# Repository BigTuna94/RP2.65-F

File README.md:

# RP2.65-F
An 65% Ortholinear Keyboard based on the Rasperry Pi RP2040 with faders.

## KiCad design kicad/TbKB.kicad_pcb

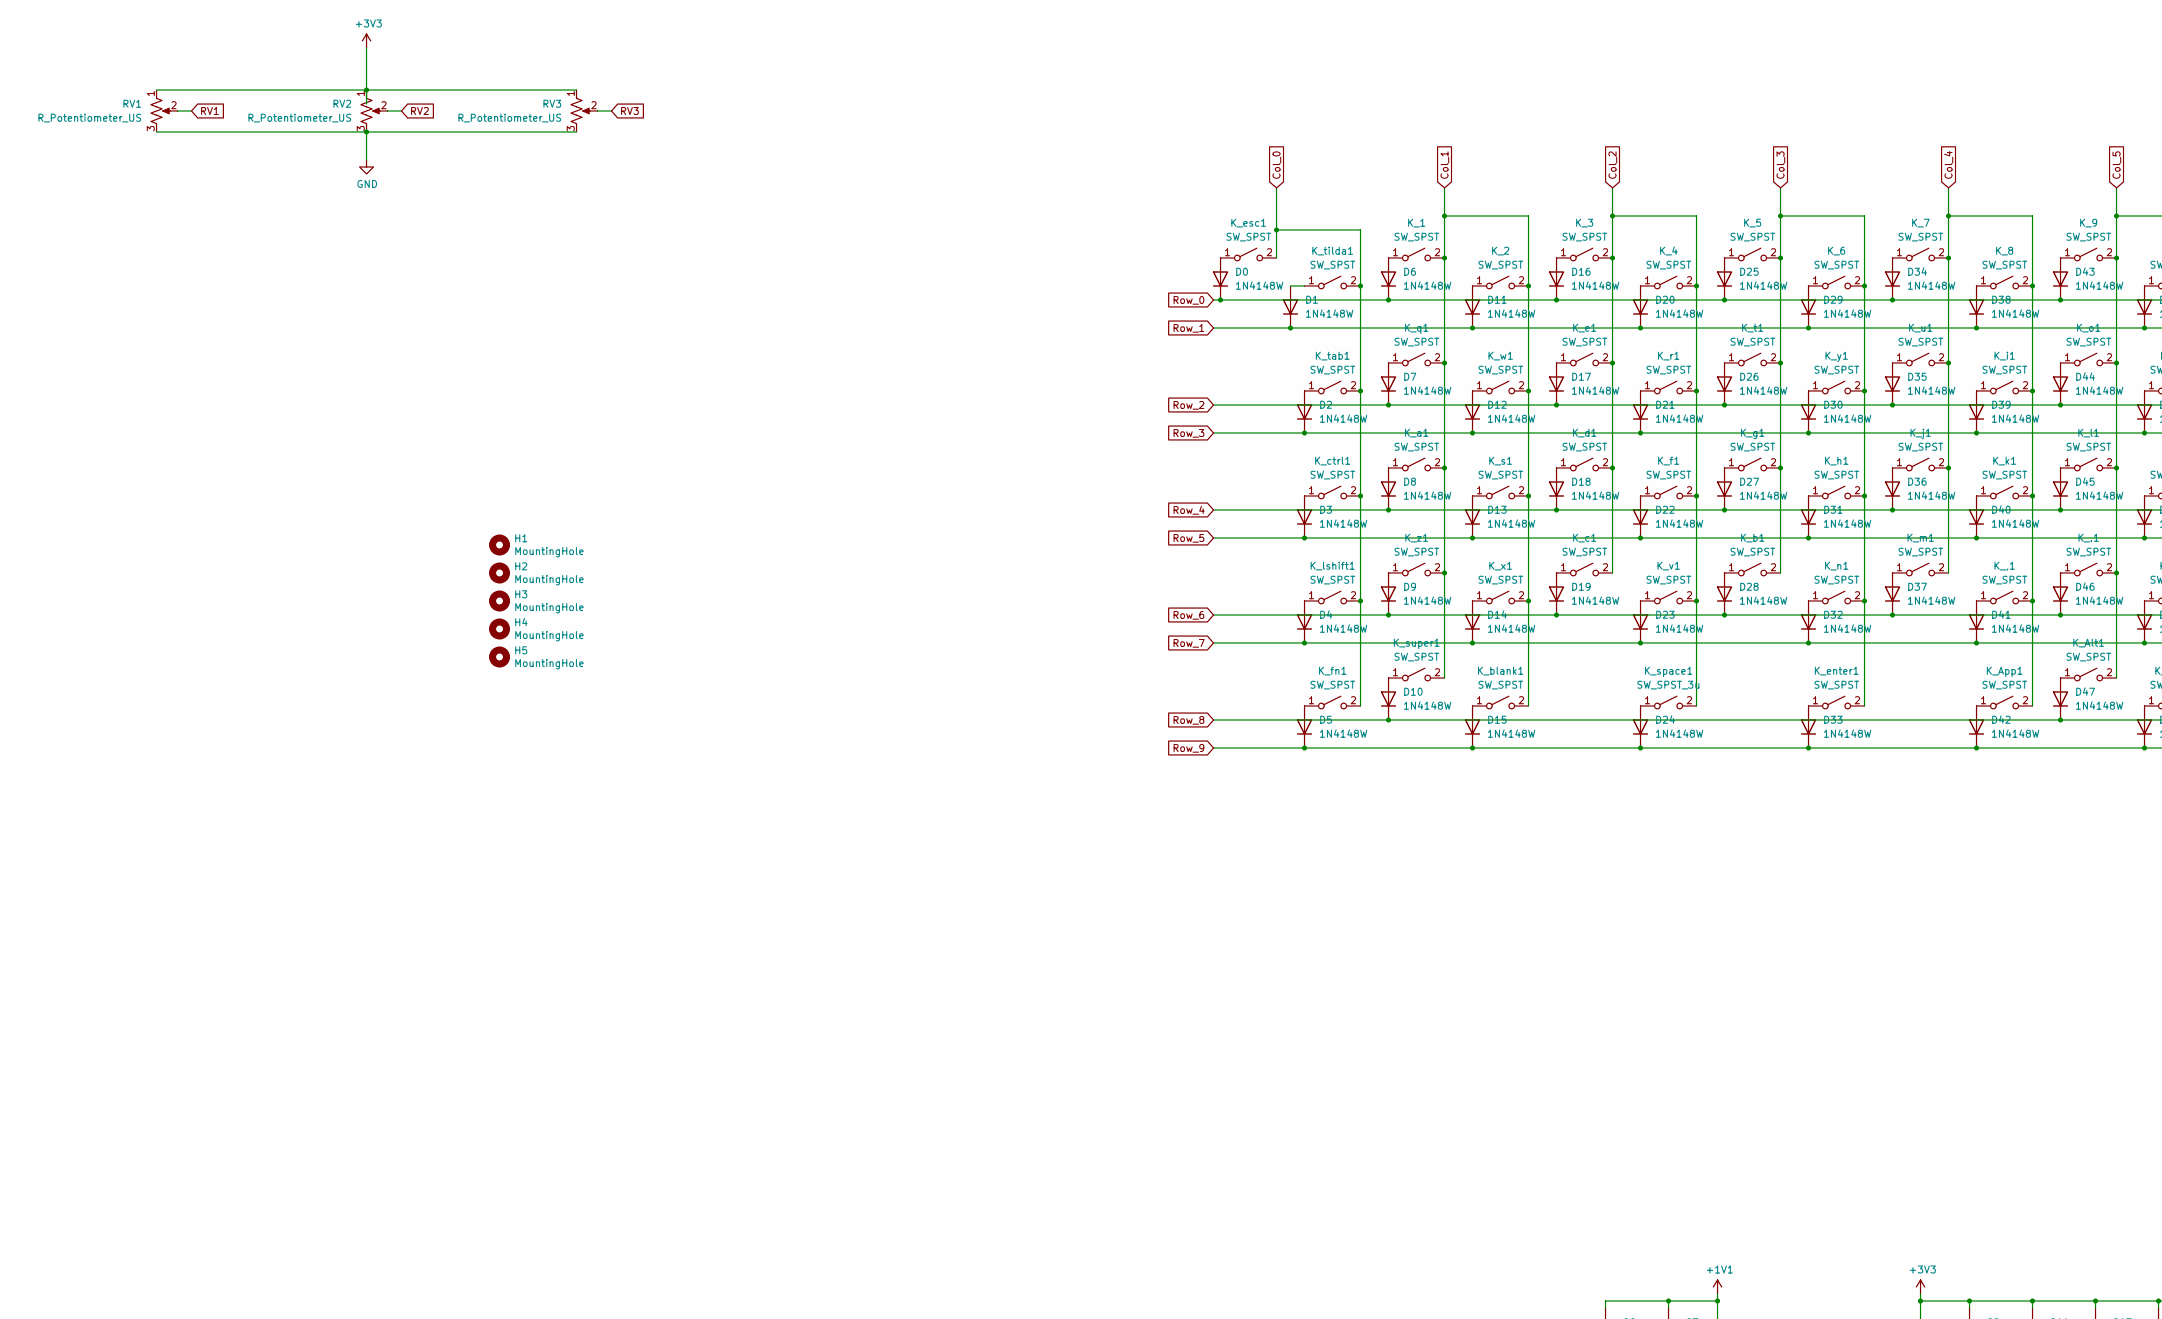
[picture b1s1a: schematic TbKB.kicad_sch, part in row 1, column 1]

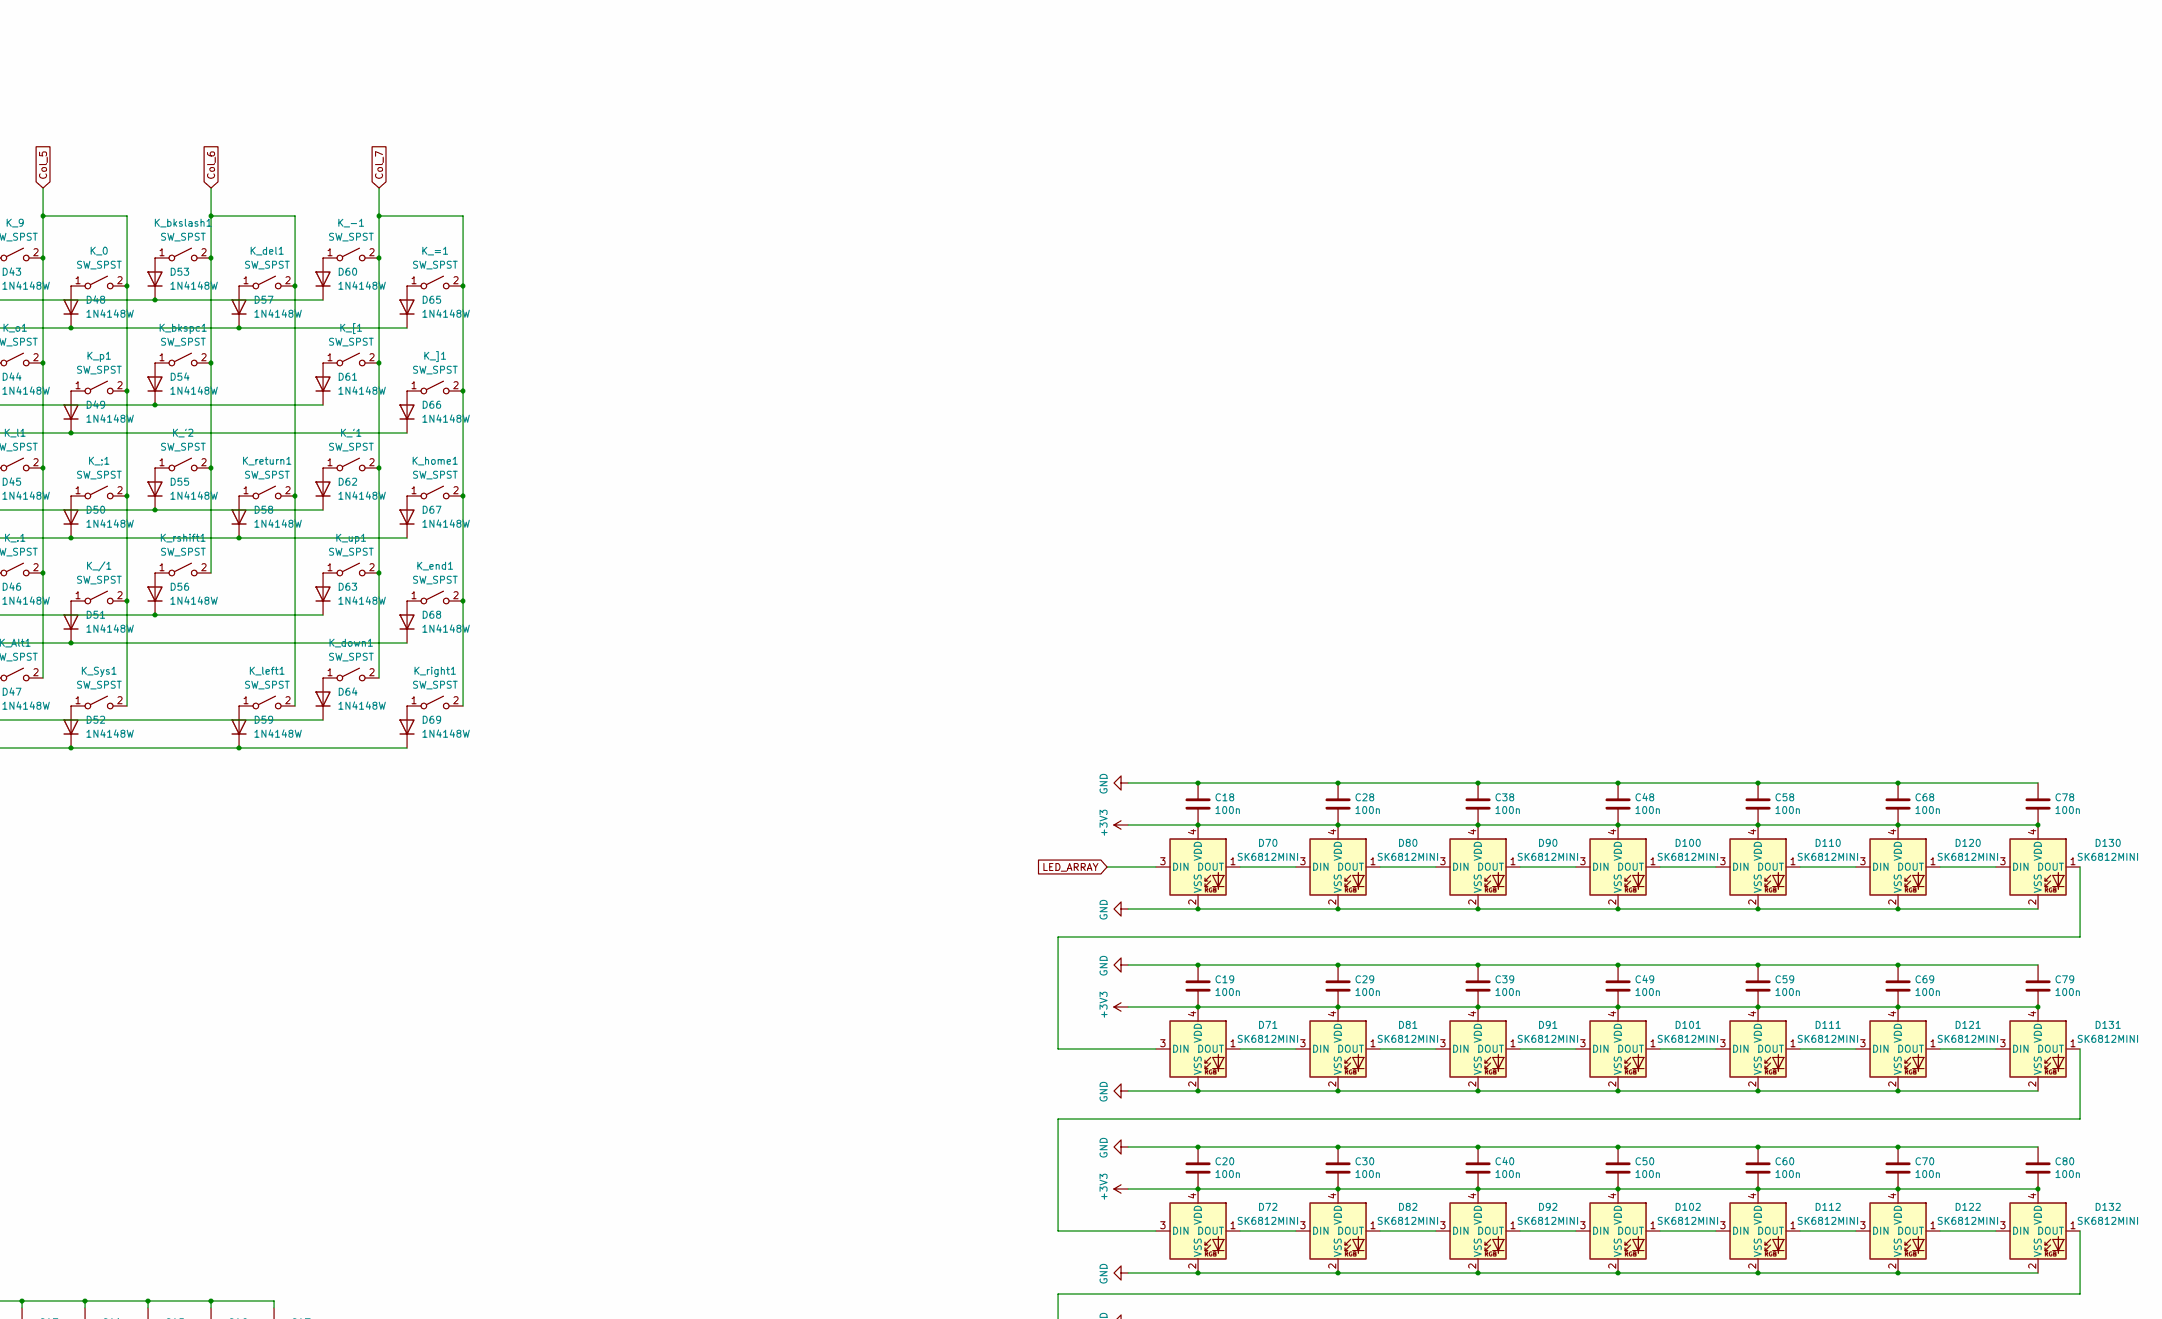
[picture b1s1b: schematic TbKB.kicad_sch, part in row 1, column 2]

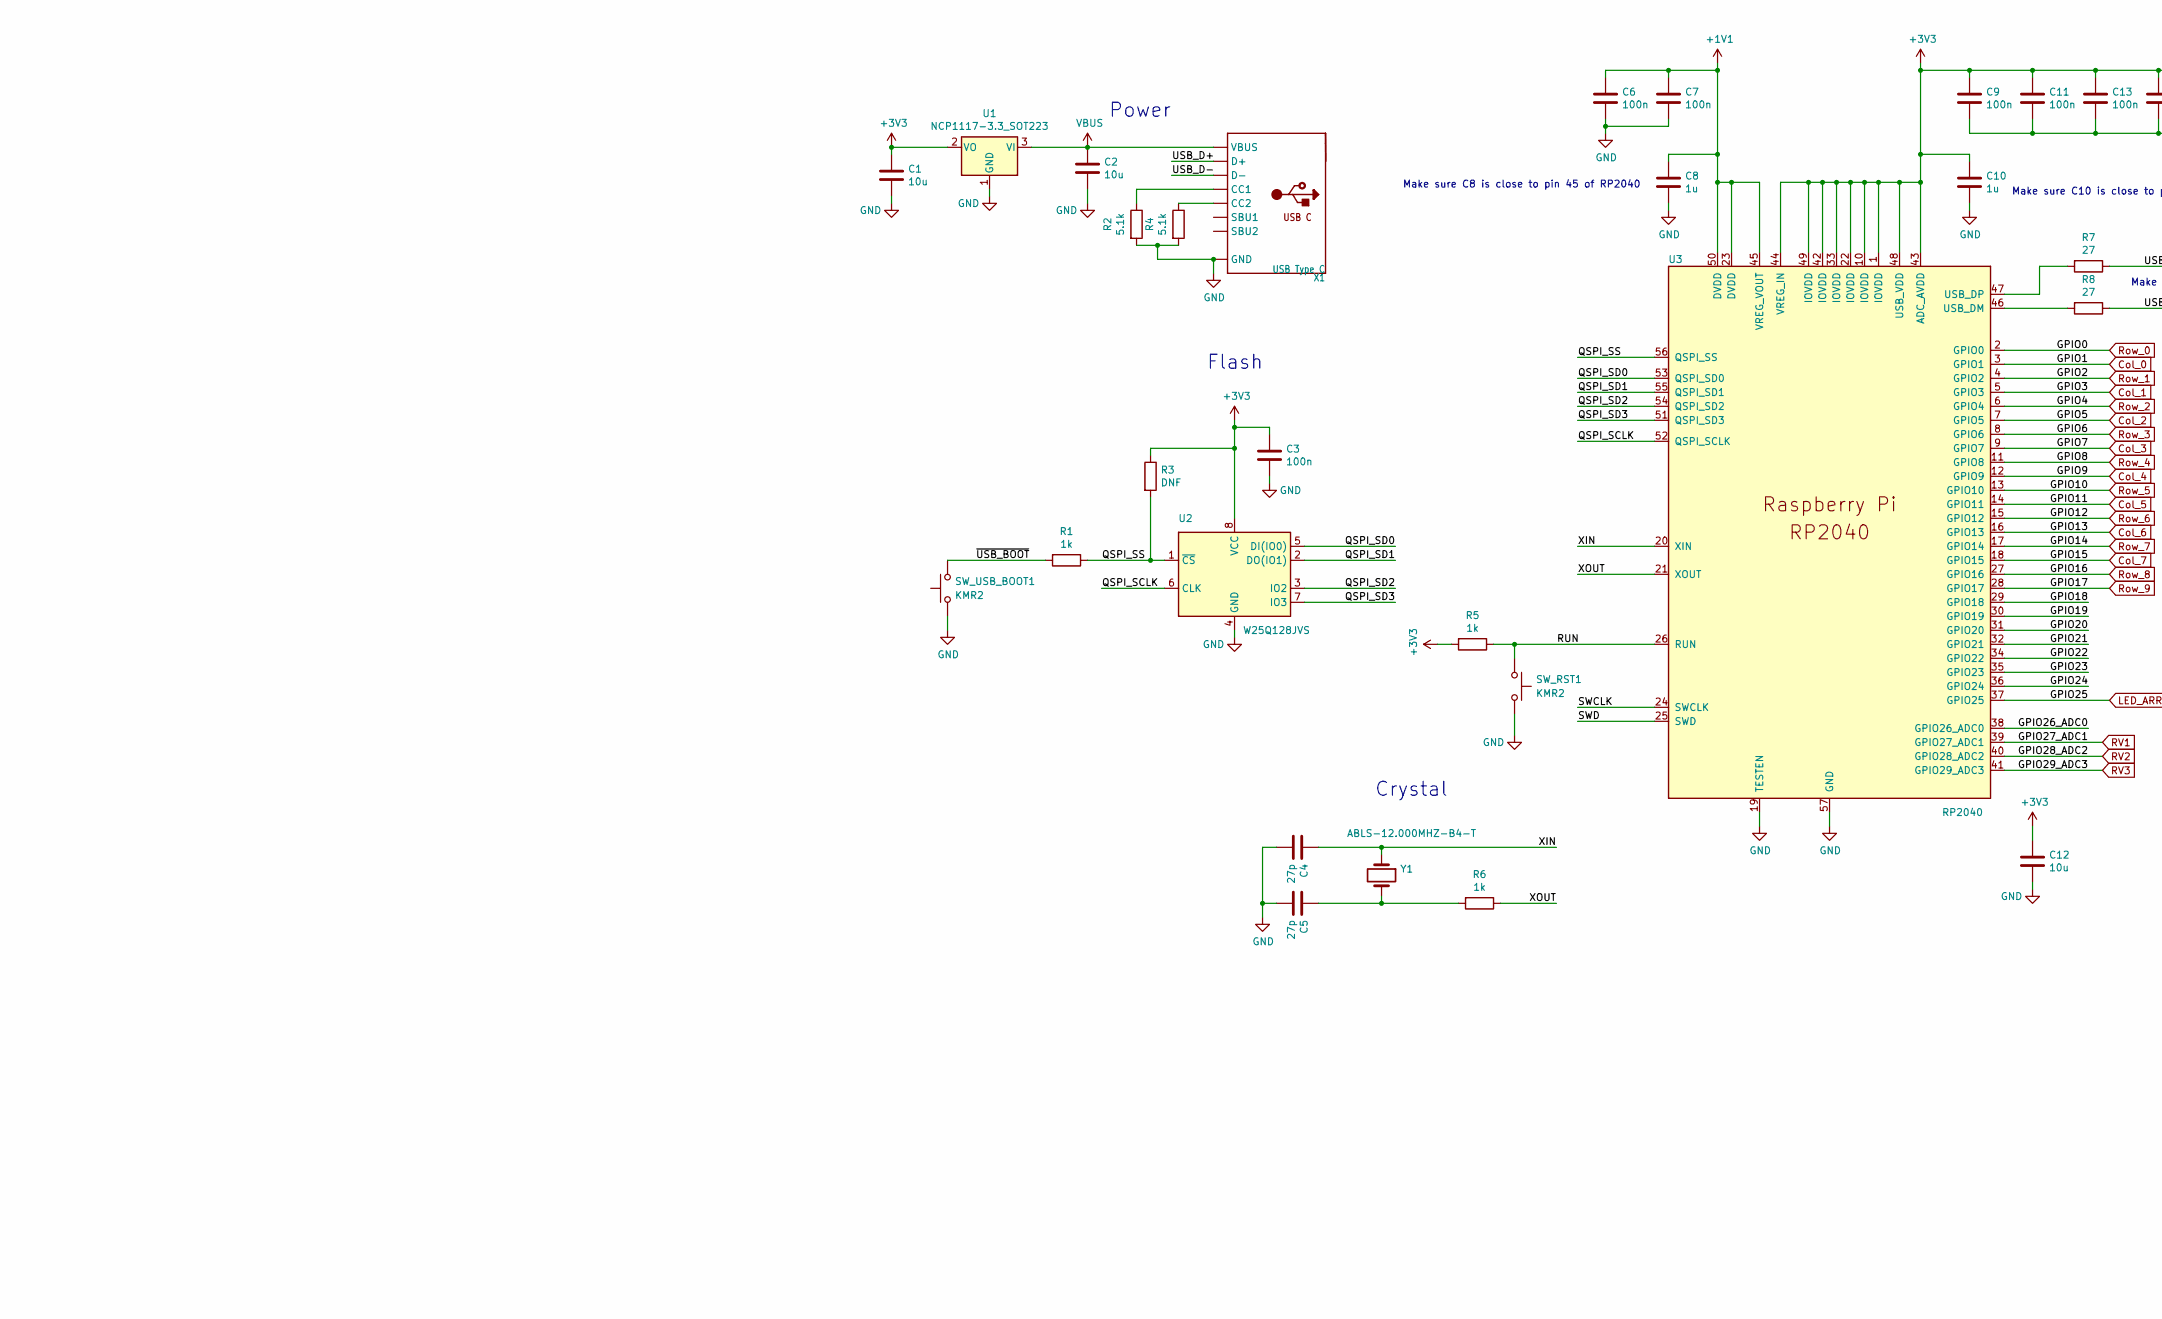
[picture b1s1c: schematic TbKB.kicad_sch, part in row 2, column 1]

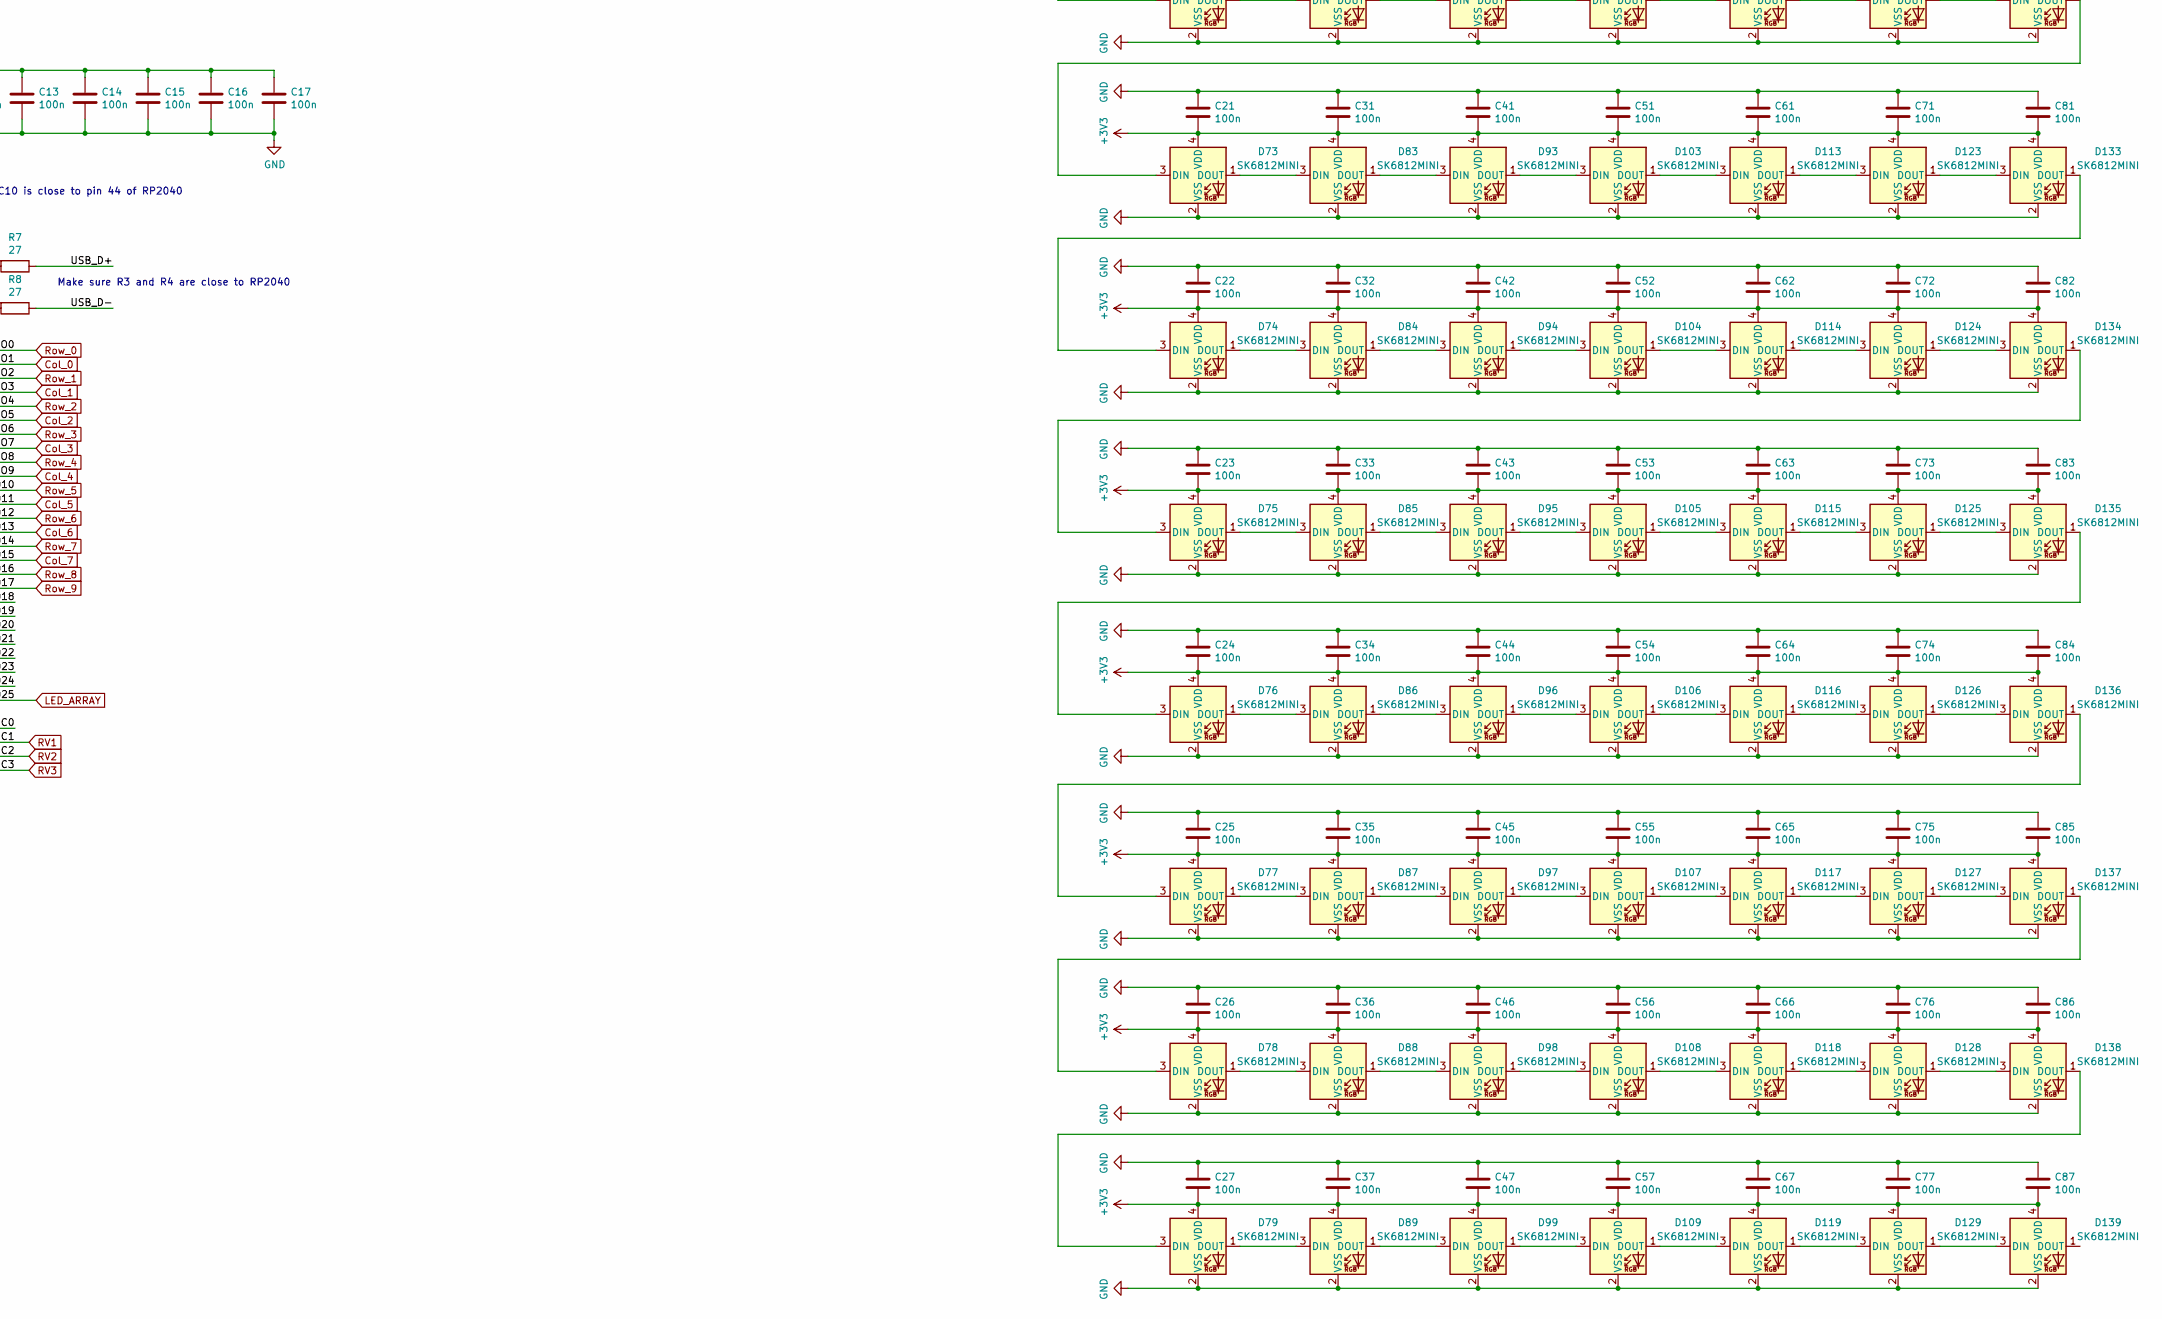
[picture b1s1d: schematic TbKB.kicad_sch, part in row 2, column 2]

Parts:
C1, C2, C12: 10u; C_0805_2012Metric
C3, C6, C7, C9, C11, C13, C14, C15, C16, C17, C18, C19, C20, C21, C22, C23, C24, C25, C26, C27, C28, C29, C30, C31, C32, C33, C34, C35, C36, C37, C38, C39, C40, C41, C42, C43, C44, C45, C46, C47, C48, C49, C50, C51, C52, C53, C54, C55, C56, C57, C58, C59, C60, C61, C62, C63, C64, C65, C66, C67, C68, C69, C70, C71, C72, C73, C74, C75, C76, C77, C78, C79, C80, C81, C82, C83, C84, C85, C86, C87: 100n; C_0402_1005Metric
C4, C5: 27p; C_0402_1005Metric
C8, C10: 1u; C_0402_1005Metric
D0, D1, D2, D3, D4, D5, D6, D7, D8, D9, D10, D11, D12, D13, D14, D15, D16, D17, D18, D19, D20, D21, D22, D23, D24, D25, D26, D27, D28, D29, D30, D31, D32, D33, D34, D35, D36, D37, D38, D39, D40, D41, D42, D43, D44, D45, D46, D47, D48, D49, D50, D51, D52, D53, D54, D55, D56, D57, D58, D59, D60, D61, D62, D63, D64, D65, D66, D67, D68, D69: 1N4148W; D_SOD-123F
D70, D71, D72, D73, D74, D75, D76, D77, D78, D79, D80, D81, D82, D83, D84, D85, D86, D87, D88, D89, D90, D91, D92, D93, D94, D95, D96, D97, D98, D99, D100, D101, D102, D103, D104, D105, D106, D107, D108, D109, D110, D111, D112, D113, D114, D115, D116, D117, D118, D119, D120, D121, D122, D123, D124, D125, D126, D127, D128, D129, D130, D131, D132, D133, D134, D135, D136, D137, D138, D139: SK6812MINI; LED_SK6812MINI_PLCC4_3.5x3.5mm_P1.75mm
H1, H2, H3, H4, H5: MountingHole; MountingHole_2.2mm_M2_Pad_Via
K_0, K_1, K_2, K_3, K_4, K_5, K_6, K_7, K_8, K_9, K_.1: SW_SPST; Kailh_socket_MX_1u
K_'1, K_'2: SW_SPST; Kailh_socket_MX_1u
K_,1: SW_SPST; Kailh_socket_MX_1u
K_-1: SW_SPST; Kailh_socket_MX_1u
K_/1: SW_SPST; Kailh_socket_MX_1u
K_;1: SW_SPST; Kailh_socket_MX_1u
K_=1: SW_SPST; Kailh_socket_MX_1u
K_Alt1: SW_SPST; Kailh_socket_MX_1.25u
K_App1: SW_SPST; Kailh_socket_MX_1u
K_Sys1: SW_SPST; Kailh_socket_MX_1u
K_[1: SW_SPST; Kailh_socket_MX_1u
K_]1: SW_SPST; Kailh_socket_MX_1u
K_a1: SW_SPST; Kailh_socket_MX_1u
K_b1: SW_SPST; Kailh_socket_MX_1u
K_bkslash1: SW_SPST; Kailh_socket_MX_1u
K_bkspc1: SW_SPST; Kailh_socket_MX_2u
K_blank1: SW_SPST; Kailh_socket_MX_1u
K_c1: SW_SPST; Kailh_socket_MX_1u
K_ctrl1: SW_SPST; Kailh_socket_MX_1.5u
K_d1: SW_SPST; Kailh_socket_MX_1u
K_del1: SW_SPST; Kailh_socket_MX_1u
K_down1: SW_SPST; Kailh_socket_MX_1u
K_e1: SW_SPST; Kailh_socket_MX_1u
K_end1: SW_SPST; Kailh_socket_MX_1u
K_enter1: SW_SPST; Kailh_socket_MX_2.25u
K_esc1: SW_SPST; Kailh_socket_MX_1u
K_f1: SW_SPST; Kailh_socket_MX_1u
K_fn1: SW_SPST; Kailh_socket_MX_1u
K_g1: SW_SPST; Kailh_socket_MX_1u
K_h1: SW_SPST; Kailh_socket_MX_1u
K_home1: SW_SPST; Kailh_socket_MX_1u
K_i1: SW_SPST; Kailh_socket_MX_1u
K_j1: SW_SPST; Kailh_socket_MX_1u
K_k1: SW_SPST; Kailh_socket_MX_1u
K_l1: SW_SPST; Kailh_socket_MX_1u
K_left1: SW_SPST; Kailh_socket_MX_1u
K_lshift1: SW_SPST; Kailh_socket_MX_1.25u
K_m1: SW_SPST; Kailh_socket_MX_1u
K_n1: SW_SPST; Kailh_socket_MX_1u
K_o1: SW_SPST; Kailh_socket_MX_1u
K_p1: SW_SPST; Kailh_socket_MX_1u
K_q1: SW_SPST; Kailh_socket_MX_1u
K_r1: SW_SPST; Kailh_socket_MX_1u
K_return1: SW_SPST; Kailh_socket_MX_1u
K_right1: SW_SPST; Kailh_socket_MX_1u
K_rshift1: SW_SPST; Kailh_socket_MX_1.5u
K_s1: SW_SPST; Kailh_socket_MX_1u
K_space1: SW_SPST_3u; Kailh_socket_MX_1u
K_super1: SW_SPST; Kailh_socket_MX_1.5u
K_t1: SW_SPST; Kailh_socket_MX_1u
K_tab1: SW_SPST; Kailh_socket_MX_1.5u
K_tilda1: SW_SPST; Kailh_socket_MX_1u
K_u1: SW_SPST; Kailh_socket_MX_1u
K_up1: SW_SPST; Kailh_socket_MX_1u
K_v1: SW_SPST; Kailh_socket_MX_1u
K_w1: SW_SPST; Kailh_socket_MX_1u
K_x1: SW_SPST; Kailh_socket_MX_1u
K_y1: SW_SPST; Kailh_socket_MX_1u
K_z1: SW_SPST; Kailh_socket_MX_1u
R1, R5, R6: 1k; C_0402_1005Metric
R2, R4: 5.1k; C_0402_1005Metric
R3: DNF; C_0402_1005Metric
R7, R8: 27; C_0402_1005Metric
RV1, RV2, RV3: R_Potentiometer_US; Potentiometer_Bourns_PTA6043_Single_Slide
SW_RST1: KMR2; SW_Push_1P1T_NO_CK_KMR2
SW_USB_BOOT1: KMR2; SW_Push_1P1T_NO_CK_KMR2
U1: NCP1117-3.3_SOT223; SOT-223-3_TabPin2
U2: W25Q128JVS; SOIC-8_5.23x5.23mm_P1.27mm
U3: RP2040; RP2040-QFN-56
X1: USB Type C; USB_C_CUSB31-CFM2AX-01-X
Y1: ABLS-12.000MHZ-B4-T; Crystal_SMD_HC49-US

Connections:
+1V1: C6.1, C7.1, C8.1, U3.23 (DVDD), U3.45 (VREG_VOUT), U3.50 (DVDD)
+3V3: C1.1, C3.1, C9.1, C10.1, C11.1, C12.1, C13.1, C14.1, C15.1, C16.1, C17.1, C18.2, C19.2, C20.2, C21.2, C22.2, C23.2, C24.2, C25.2, C26.2, C27.2, C28.2, C29.2, C30.2, C31.2, C32.2, C33.2, C34.2, C35.2, C36.2, C37.2, C38.2, C39.2, C40.2, C41.2, C42.2, C43.2, C44.2, C45.2, C46.2, C47.2, C48.2, C49.2, C50.2, C51.2, C52.2, C53.2, C54.2, C55.2, C56.2, C57.2, C58.2, C59.2, C60.2, C61.2, C62.2, C63.2, C64.2, C65.2, C66.2, C67.2, C68.2, C69.2, C70.2, C71.2, C72.2, C73.2, C74.2, C75.2, C76.2, C77.2, C78.2, C79.2, C80.2, C81.2, C82.2, C83.2, C84.2, C85.2, C86.2, C87.2, D70.4 (VDD), D71.4 (VDD), D72.4 (VDD), D73.4 (VDD), D74.4 (VDD), D75.4 (VDD), D76.4 (VDD), D77.4 (VDD), D78.4 (VDD), D79.4 (VDD), D80.4 (VDD), D81.4 (VDD), D82.4 (VDD), D83.4 (VDD), D84.4 (VDD), D85.4 (VDD), D86.4 (VDD), D87.4 (VDD), D88.4 (VDD), D89.4 (VDD), D90.4 (VDD), D91.4 (VDD), D92.4 (VDD), D93.4 (VDD), D94.4 (VDD), D95.4 (VDD), D96.4 (VDD), D97.4 (VDD), D98.4 (VDD), D99.4 (VDD), D100.4 (VDD), D101.4 (VDD), D102.4 (VDD), D103.4 (VDD), D104.4 (VDD), D105.4 (VDD), D106.4 (VDD), D107.4 (VDD), D108.4 (VDD), D109.4 (VDD), D110.4 (VDD), D111.4 (VDD), D112.4 (VDD), D113.4 (VDD), D114.4 (VDD), D115.4 (VDD), D116.4 (VDD), D117.4 (VDD), D118.4 (VDD), D119.4 (VDD), D120.4 (VDD), D121.4 (VDD), D122.4 (VDD), D123.4 (VDD), D124.4 (VDD), D125.4 (VDD), D126.4 (VDD), D127.4 (VDD), D128.4 (VDD), D129.4 (VDD), D130.4 (VDD), D131.4 (VDD), D132.4 (VDD), D133.4 (VDD), D134.4 (VDD), D135.4 (VDD), D136.4 (VDD), D137.4 (VDD), D138.4 (VDD), D139.4 (VDD), R3.1, R5.2, RV1.1, RV2.1, RV3.1, U1.2 (VO), U2.8 (VCC), U3.1 (IOVDD), U3.10 (IOVDD), U3.22 (IOVDD), U3.33 (IOVDD), U3.42 (IOVDD), U3.43 (ADC_AVDD), U3.44 (VREG_IN), U3.48 (USB_VDD), U3.49 (IOVDD)
/GPIO18: U3.29 (GPIO18)
/GPIO19: U3.30 (GPIO19)
/GPIO20: U3.31 (GPIO20)
/GPIO21: U3.32 (GPIO21)
/GPIO22: U3.34 (GPIO22)
/GPIO23: U3.35 (GPIO23)
/GPIO24: U3.36 (GPIO24)
/GPIO26_ADC0: U3.38 (GPIO26_ADC0)
/QSPI_SCLK: U2.6 (CLK), U3.52 (QSPI_SCLK)
/QSPI_SD0: U2.5 (DI(IO0)), U3.53 (QSPI_SD0)
/QSPI_SD1: U2.2 (DO(IO1)), U3.55 (QSPI_SD1)
/QSPI_SD2: U2.3 (IO2), U3.54 (QSPI_SD2)
/QSPI_SD3: U2.7 (IO3), U3.51 (QSPI_SD3)
/QSPI_SS: R1.1, R3.2, U2.1 (~CS), U3.56 (QSPI_SS)
/RUN: R5.1, SW_RST1.1, U3.26 (RUN)
/SWCLK: U3.24 (SWCLK)
/SWD: U3.25 (SWD)
/USB_D+: R7.1, X1.A6 (D+), X1.B6 (D+)
/USB_D-: R8.1, X1.A7 (D-), X1.B7 (D-)
/XIN: C4.1, U3.20 (XIN), Y1.1
/XOUT: R6.1, U3.21 (XOUT)
/~USB_BOOT: R1.2, SW_USB_BOOT1.2
Col_0: K_ctrl1.2 (B), K_esc1.2 (B), K_fn1.2 (B), K_lshift1.2 (B), K_tab1.2 (B), K_tilda1.2 (B), U3.3 (GPIO1)
Col_1: K_1.2 (B), K_2.2 (B), K_a1.2 (B), K_blank1.2 (B), K_q1.2 (B), K_s1.2 (B), K_super1.2 (B), K_w1.2 (B), K_x1.2 (B), K_z1.2 (B), U3.5 (GPIO3)
Col_2: K_3.2 (B), K_4.2 (B), K_c1.2 (B), K_d1.2 (B), K_e1.2 (B), K_f1.2 (B), K_r1.2 (B), K_space1.2 (B), K_v1.2 (B), U3.7 (GPIO5); also elsewhere on the board
Col_3: K_5.2 (B), K_6.2 (B), K_b1.2 (B), K_enter1.2 (B), K_g1.2 (B), K_h1.2 (B), K_n1.2 (B), K_t1.2 (B), K_y1.2 (B), U3.9 (GPIO7); also elsewhere on the board
Col_4: K_7.2 (B), K_8.2 (B), K_,1.2 (B), K_App1.2 (B), K_i1.2 (B), K_j1.2 (B), K_k1.2 (B), K_m1.2 (B), K_u1.2 (B), U3.12 (GPIO9)
Col_5: K_0.2 (B), K_9.2 (B), K_.1.2 (B), K_/1.2 (B), K_;1.2 (B), K_Alt1.2 (B), K_Sys1.2 (B), K_l1.2 (B), K_o1.2 (B), K_p1.2 (B), U3.14 (GPIO11)
Col_6: K_'2.2 (B), K_bkslash1.2 (B), K_bkspc1.2 (B), K_del1.2 (B), K_left1.2 (B), K_return1.2 (B), K_rshift1.2 (B), U3.16 (GPIO13); also elsewhere on the board
Col_7: K_'1.2 (B), K_-1.2 (B), K_=1.2 (B), K_[1.2 (B), K_]1.2 (B), K_down1.2 (B), K_end1.2 (B), K_home1.2 (B), K_right1.2 (B), K_up1.2 (B), U3.18 (GPIO15)
GND: C1.2, C2.2, C3.2, C4.2, C5.2, C6.2, C7.2, C8.2, C9.2, C10.2, C11.2, C12.2, C13.2, C14.2, C15.2, C16.2, C17.2, C18.1, C19.1, C20.1, C21.1, C22.1, C23.1, C24.1, C25.1, C26.1, C27.1, C28.1, C29.1, C30.1, C31.1, C32.1, C33.1, C34.1, C35.1, C36.1, C37.1, C38.1, C39.1, C40.1, C41.1, C42.1, C43.1, C44.1, C45.1, C46.1, C47.1, C48.1, C49.1, C50.1, C51.1, C52.1, C53.1, C54.1, C55.1, C56.1, C57.1, C58.1, C59.1, C60.1, C61.1, C62.1, C63.1, C64.1, C65.1, C66.1, C67.1, C68.1, C69.1, C70.1, C71.1, C72.1, C73.1, C74.1, C75.1, C76.1, C77.1, C78.1, C79.1, C80.1, C81.1, C82.1, C83.1, C84.1, C85.1, C86.1, C87.1, D70.2 (VSS), D71.2 (VSS), D72.2 (VSS), D73.2 (VSS), D74.2 (VSS), D75.2 (VSS), D76.2 (VSS), D77.2 (VSS), D78.2 (VSS), D79.2 (VSS), D80.2 (VSS), D81.2 (VSS), D82.2 (VSS), D83.2 (VSS), D84.2 (VSS), D85.2 (VSS), D86.2 (VSS), D87.2 (VSS), D88.2 (VSS), D89.2 (VSS), D90.2 (VSS), D91.2 (VSS), D92.2 (VSS), D93.2 (VSS), D94.2 (VSS), D95.2 (VSS), D96.2 (VSS), D97.2 (VSS), D98.2 (VSS), D99.2 (VSS), D100.2 (VSS), D101.2 (VSS), D102.2 (VSS), D103.2 (VSS), D104.2 (VSS), D105.2 (VSS), D106.2 (VSS), D107.2 (VSS), D108.2 (VSS), D109.2 (VSS), D110.2 (VSS), D111.2 (VSS), D112.2 (VSS), D113.2 (VSS), D114.2 (VSS), D115.2 (VSS), D116.2 (VSS), D117.2 (VSS), D118.2 (VSS), D119.2 (VSS), D120.2 (VSS), D121.2 (VSS), D122.2 (VSS), D123.2 (VSS), D124.2 (VSS), D125.2 (VSS), D126.2 (VSS), D127.2 (VSS), D128.2 (VSS), D129.2 (VSS), D130.2 (VSS), D131.2 (VSS), D132.2 (VSS), D133.2 (VSS), D134.2 (VSS), D135.2 (VSS), D136.2 (VSS), D137.2 (VSS), D138.2 (VSS), D139.2 (VSS), R2.2, R4.2, RV1.3, RV2.3, RV3.3, SW_RST1.2, SW_USB_BOOT1.1, U1.1 (GND), U2.4 (GND), U3.19 (TESTEN), U3.57 (GND), X1.A1B12 (GND), X1.B1A12 (GND)
LED_ARRAY: D70.3 (DIN), U3.37 (GPIO25)
unnamed: C5.1, R6.2, Y1.2
unnamed: D0.2 (A), K_esc1.1 (A)
unnamed: D1.2 (A), K_tilda1.1 (A)
unnamed: D2.2 (A), K_tab1.1 (A)
unnamed: D3.2 (A), K_ctrl1.1 (A)
unnamed: D4.2 (A), K_lshift1.1 (A)
unnamed: D5.2 (A), K_fn1.1 (A)
unnamed: D6.2 (A), K_1.1 (A)
unnamed: D7.2 (A), K_q1.1 (A)
unnamed: D8.2 (A), K_a1.1 (A)
unnamed: D9.2 (A), K_z1.1 (A)
unnamed: D10.2 (A), K_super1.1 (A)
unnamed: D11.2 (A), K_2.1 (A)
unnamed: D12.2 (A), K_w1.1 (A)
unnamed: D13.2 (A), K_s1.1 (A)
unnamed: D14.2 (A), K_x1.1 (A)
unnamed: D15.2 (A), K_blank1.1 (A)
unnamed: D16.2 (A), K_3.1 (A)
unnamed: D17.2 (A), K_e1.1 (A)
unnamed: D18.2 (A), K_d1.1 (A)
unnamed: D19.2 (A), K_c1.1 (A)
unnamed: D20.2 (A), K_4.1 (A)
unnamed: D21.2 (A), K_r1.1 (A)
unnamed: D22.2 (A), K_f1.1 (A)
unnamed: D23.2 (A), K_v1.1 (A)
unnamed 59: D24.2 (A), K_space1.1 (A); also elsewhere on the board
unnamed: D25.2 (A), K_5.1 (A)
unnamed: D26.2 (A), K_t1.1 (A)
unnamed: D27.2 (A), K_g1.1 (A)
unnamed: D28.2 (A), K_b1.1 (A)
unnamed: D29.2 (A), K_6.1 (A)
unnamed: D30.2 (A), K_y1.1 (A)
unnamed: D31.2 (A), K_h1.1 (A)
unnamed: D32.2 (A), K_n1.1 (A)
unnamed 68: D33.2 (A), K_enter1.1 (A); also elsewhere on the board
unnamed: D34.2 (A), K_7.1 (A)
unnamed: D35.2 (A), K_u1.1 (A)
unnamed: D36.2 (A), K_j1.1 (A)
unnamed: D37.2 (A), K_m1.1 (A)
unnamed: D38.2 (A), K_8.1 (A)
unnamed: D39.2 (A), K_i1.1 (A)
unnamed: D40.2 (A), K_k1.1 (A)
unnamed: D41.2 (A), K_,1.1 (A)
unnamed: D42.2 (A), K_App1.1 (A)
unnamed: D43.2 (A), K_9.1 (A)
unnamed: D44.2 (A), K_o1.1 (A)
unnamed: D45.2 (A), K_l1.1 (A)
unnamed: D46.2 (A), K_.1.1 (A)
unnamed: D47.2 (A), K_Alt1.1 (A)
unnamed: D48.2 (A), K_0.1 (A)
unnamed: D49.2 (A), K_p1.1 (A)
unnamed: D50.2 (A), K_;1.1 (A)
unnamed: D51.2 (A), K_/1.1 (A)
unnamed: D52.2 (A), K_Sys1.1 (A)
unnamed: D53.2 (A), K_bkslash1.1 (A)
unnamed 89: D54.2 (A), K_bkspc1.1 (A); also elsewhere on the board
unnamed: D55.2 (A), K_'2.1 (A)
unnamed 91: D56.2 (A), K_rshift1.1 (A); also elsewhere on the board
unnamed: D57.2 (A), K_del1.1 (A)
unnamed 93: D58.2 (A), K_return1.1 (A); also elsewhere on the board
unnamed: D59.2 (A), K_left1.1 (A)
unnamed: D60.2 (A), K_-1.1 (A)
unnamed: D61.2 (A), K_[1.1 (A)
unnamed: D62.2 (A), K_'1.1 (A)
unnamed: D63.2 (A), K_up1.1 (A)
unnamed: D64.2 (A), K_down1.1 (A)
unnamed: D65.2 (A), K_=1.1 (A)
unnamed: D66.2 (A), K_]1.1 (A)
unnamed: D67.2 (A), K_home1.1 (A)
unnamed: D68.2 (A), K_end1.1 (A)
unnamed: D69.2 (A), K_right1.1 (A)
unnamed: D70.1 (DOUT), D80.3 (DIN)
unnamed: D71.1 (DOUT), D81.3 (DIN)
unnamed: D72.1 (DOUT), D82.3 (DIN)
unnamed: D73.1 (DOUT), D83.3 (DIN)
unnamed: D74.1 (DOUT), D84.3 (DIN)
unnamed: D75.1 (DOUT), D85.3 (DIN)
unnamed: D76.1 (DOUT), D86.3 (DIN)
unnamed: D77.1 (DOUT), D87.3 (DIN)
unnamed: D78.1 (DOUT), D88.3 (DIN)
unnamed: D79.1 (DOUT), D89.3 (DIN)
unnamed: D80.1 (DOUT), D90.3 (DIN)
unnamed: D81.1 (DOUT), D91.3 (DIN)
unnamed: D82.1 (DOUT), D92.3 (DIN)
unnamed: D83.1 (DOUT), D93.3 (DIN)
unnamed: D84.1 (DOUT), D94.3 (DIN)
unnamed: D85.1 (DOUT), D95.3 (DIN)
unnamed: D86.1 (DOUT), D96.3 (DIN)
unnamed: D87.1 (DOUT), D97.3 (DIN)
unnamed: D88.1 (DOUT), D98.3 (DIN)
unnamed: D89.1 (DOUT), D99.3 (DIN)
unnamed: D100.1 (DOUT), D110.3 (DIN)
unnamed: D90.1 (DOUT), D100.3 (DIN)
unnamed: D101.1 (DOUT), D111.3 (DIN)
unnamed: D91.1 (DOUT), D101.3 (DIN)
unnamed: D102.1 (DOUT), D112.3 (DIN)
unnamed: D92.1 (DOUT), D102.3 (DIN)
unnamed: D103.1 (DOUT), D113.3 (DIN)
unnamed: D93.1 (DOUT), D103.3 (DIN)
unnamed: D104.1 (DOUT), D114.3 (DIN)
unnamed: D94.1 (DOUT), D104.3 (DIN)
unnamed: D105.1 (DOUT), D115.3 (DIN)
unnamed: D95.1 (DOUT), D105.3 (DIN)
unnamed: D106.1 (DOUT), D116.3 (DIN)
unnamed: D96.1 (DOUT), D106.3 (DIN)
unnamed: D107.1 (DOUT), D117.3 (DIN)
unnamed: D97.1 (DOUT), D107.3 (DIN)
unnamed: D108.1 (DOUT), D118.3 (DIN)
unnamed: D98.1 (DOUT), D108.3 (DIN)
unnamed: D109.1 (DOUT), D119.3 (DIN)
unnamed: D99.1 (DOUT), D109.3 (DIN)
unnamed: D110.1 (DOUT), D120.3 (DIN)
unnamed: D111.1 (DOUT), D121.3 (DIN)
unnamed: D112.1 (DOUT), D122.3 (DIN)
unnamed: D113.1 (DOUT), D123.3 (DIN)
unnamed: D114.1 (DOUT), D124.3 (DIN)
unnamed: D115.1 (DOUT), D125.3 (DIN)
unnamed: D116.1 (DOUT), D126.3 (DIN)
unnamed: D117.1 (DOUT), D127.3 (DIN)
unnamed: D118.1 (DOUT), D128.3 (DIN)
unnamed: D119.1 (DOUT), D129.3 (DIN)
unnamed: D120.1 (DOUT), D130.3 (DIN)
unnamed: D121.1 (DOUT), D131.3 (DIN)
unnamed: D122.1 (DOUT), D132.3 (DIN)
unnamed: D123.1 (DOUT), D133.3 (DIN)
unnamed: D124.1 (DOUT), D134.3 (DIN)
unnamed: D125.1 (DOUT), D135.3 (DIN)
unnamed: D126.1 (DOUT), D136.3 (DIN)
unnamed: D127.1 (DOUT), D137.3 (DIN)
unnamed: D128.1 (DOUT), D138.3 (DIN)
unnamed: D129.1 (DOUT), D139.3 (DIN)
unnamed: D71.3 (DIN), D130.1 (DOUT)
unnamed: D72.3 (DIN), D131.1 (DOUT)
unnamed: D73.3 (DIN), D132.1 (DOUT)
unnamed: D74.3 (DIN), D133.1 (DOUT)
unnamed: D75.3 (DIN), D134.1 (DOUT)
unnamed: D76.3 (DIN), D135.1 (DOUT)
unnamed: D77.3 (DIN), D136.1 (DOUT)
unnamed: D78.3 (DIN), D137.1 (DOUT)
unnamed: D79.3 (DIN), D138.1 (DOUT)
unnamed: R2.1, X1.A5 (CC1)
unnamed: R4.1, X1.B5 (CC2)
unnamed: R7.2, U3.47 (USB_DP)
unnamed: R8.2, U3.46 (USB_DM)
RV1: RV1.2, U3.39 (GPIO27_ADC1)
RV2: RV2.2, U3.40 (GPIO28_ADC2)
RV3: RV3.2, U3.41 (GPIO29_ADC3)
Row_0: D0.1 (K), D6.1 (K), D16.1 (K), D25.1 (K), D34.1 (K), D43.1 (K), D53.1 (K), D60.1 (K), U3.2 (GPIO0)
Row_1: D1.1 (K), D11.1 (K), D20.1 (K), D29.1 (K), D38.1 (K), D48.1 (K), D57.1 (K), D65.1 (K), U3.4 (GPIO2)
Row_2: D7.1 (K), D17.1 (K), D26.1 (K), D35.1 (K), D44.1 (K), D54.1 (K), D61.1 (K), U3.6 (GPIO4)
Row_3: D2.1 (K), D12.1 (K), D21.1 (K), D30.1 (K), D39.1 (K), D49.1 (K), D66.1 (K), U3.8 (GPIO6)
Row_4: D8.1 (K), D18.1 (K), D27.1 (K), D36.1 (K), D45.1 (K), D55.1 (K), D62.1 (K), U3.11 (GPIO8)
Row_5: D3.1 (K), D13.1 (K), D22.1 (K), D31.1 (K), D40.1 (K), D50.1 (K), D58.1 (K), D67.1 (K), U3.13 (GPIO10)
Row_6: D9.1 (K), D19.1 (K), D28.1 (K), D37.1 (K), D46.1 (K), D56.1 (K), D63.1 (K), U3.15 (GPIO12)
Row_7: D4.1 (K), D14.1 (K), D23.1 (K), D32.1 (K), D41.1 (K), D51.1 (K), D68.1 (K), U3.17 (GPIO14)
Row_8: D10.1 (K), D47.1 (K), D64.1 (K), U3.27 (GPIO16)
Row_9: D5.1 (K), D15.1 (K), D24.1 (K), D33.1 (K), D42.1 (K), D52.1 (K), D59.1 (K), D69.1 (K), U3.28 (GPIO17)
VBUS: C2.1, U1.3 (VI), X1.A4B9 (VBUS), X1.B4A9 (VBUS)

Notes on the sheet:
Crystal
Make sure C8 is close to pin 45 of RP2040
Power
Make sure C10 is close to pin 44 of RP2040
Flash
Make sure R3 and R4 are close to RP2040

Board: 2 copper layers, 329 parts (177 on the bottom side), 182 nets, no tracks yet.

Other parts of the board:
2U_STAB: Stabilizer_Cherry_MX_2.00u
3U SPACE STAB: Stabilizer_Cherry_MX_3.00u
6.25U SPACE STAB: Stabilizer_Cherry_MX_6.25u
K_Enter_2.25U: SW_SPST; Kailh_socket_MX_2.25u
K_Space_2U: SW_SPST_3u; Kailh_socket_MX_1u
K_bkspc1_2U: SW_SPST; Kailh_socket_MX_2u
K_bkspc_1.75U: SW_SPST; Kailh_socket_MX_2u
K_return_1.75U, K_return_1U: SW_SPST; Kailh_socket_MX_1u
K_rshift_1.5U, K_rshift_1.75U: SW_SPST; Kailh_socket_MX_1.5u
K_space_6.25U: SW_SPST_3u; Kailh_socket_MX_1u
U41: CherryMX_2.25U; CherryMX_2.25u_PCB_Stabilizer

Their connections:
Col_2: K_Space_2U.2 (B), K_space_6.25U.2 (B); also elsewhere on the board
Col_3: K_Enter_2.25U.2 (B); also elsewhere on the board
Col_6: K_bkspc1_2U.2 (B), K_bkspc_1.75U.2 (B), K_return_1.75U.2 (B), K_return_1U.2 (B), K_rshift_1.5U.2 (B), K_rshift_1.75U.2 (B); also elsewhere on the board
unnamed 59: K_Space_2U.1 (A), K_space_6.25U.1 (A); also elsewhere on the board
unnamed 68: K_Enter_2.25U.1 (A); also elsewhere on the board
unnamed 89: K_bkspc1_2U.1 (A), K_bkspc_1.75U.1 (A); also elsewhere on the board
unnamed 91: K_rshift_1.5U.1 (A), K_rshift_1.75U.1 (A); also elsewhere on the board
unnamed 93: K_return_1.75U.1 (A), K_return_1U.1 (A); also elsewhere on the board

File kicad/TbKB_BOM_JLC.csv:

Comment,Designator,Footprint,JLCPCB Part #
100n,"C40,C43,C21,C87,C56,C13,C78,C7,C3,C29,C15,C62,C74,C39,C65,C25,C49,C14,C55,C80,C60,C37,C30,C38,C45,C63,C85,C67,C31,C27,C58,C22,C82,C81,C9,C34,C11,C79,C41,C52,C36,C75,C48,C35,C16,C28,C73,C26,C57,C46,C44,C17,C84,C42,C20,C83,C69,C51,C59,C18,C86,C53,C76,C54,C6,C66,C61,C70,C47,C72,C19,C71,C32,C68,C77,C33,C64,C23,C24,C50",C_0402_1005Metric,
10u,"C1,C12,C2",C_0805_2012Metric,
1N4148W,"D69,D4,D12,D0,D55,D24,D37,D19,D34,D52,D32,D15,D61,D8,D62,D40,D57,D68,D63,D35,D7,D66,D36,D53,D42,D31,D17,D28,D38,D5,D45,D51,D60,D23,D50,D59,D21,D46,D54,D11,D47,D65,D22,D16,D14,D41,D49,D20,D56,D64,D9,D25,D48,D6,D43,D67,D13,D39,D44,D26,D33,D10,D58,D27,D2,D18,D1,D29,D3,D30",D_SOD-123F,
NCP1117-3.3_SOT223,U1,SOT-223-3_TabPin2,
1u,"C8,C10",C_0402_1005Metric,
1k,"R5,R1,R6",C_0402_1005Metric,
5.1k,"R4,R2",C_0402_1005Metric,
USB_C_Receptacle_HRO_TYPE-C-31-M-12,X1,USB4105-GF-A,
KMR2,"RESET,USB_BOOT",SW_Push_1P1T_NO_CK_KMR2,
W25Q128JVSIM,U2,SOIC-8_5.23x5.23mm_P1.27mm,
ECS-120-10-36B2-CWY-TR,Y1,ECS-120-10-36B2-CWY-TR,
27,"R8,R7",C_0402_1005Metric,
27p,"C4,C5",C_0402_1005Metric,
RP2040,U3,RP2040-QFN-56,
27 (DNF),R3,C_0402_1005Metric,

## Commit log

2022-01-24 Initial commit with schematic and started pcb
2022-01-30 arange pcb, switch to RP2040
2022-01-31 switched to smaller crystal, other switch fixes
2022-02-14 Added Addressable RGB leds, ancilarry capacitors, and edge cuts
2022-02-23 update LEDs, USB C, stabilizers, and mounting hole placement
2022-02-23 fix duplicate reference names for DSN export
2022-03-01 routing complete
2022-03-02 tidied up silkscreen labels
2022-03-02 corrected USB Data lines, overlapping issues, and D135 issue
2022-03-04 added sigil and board name
2022-03-04 added copper behind sigil, pre gbr fixed
2022-03-04 Added 3d models for sockets and LEDs
2022-03-04 added other 3d models, fixed crystal
2022-03-04 Switched USBC footprint out for one in stock - GTC4105
2022-03-05 Add BOM csv
2022-03-13 change switch labels too non-key specific k_<n> vals on pcb, switch USB C footprint to JLC stocked component, add BOM files
2022-03-13 update switch references to k_<n> values
2022-05-02 add keyboard image
2022-05-02 add image to readme
